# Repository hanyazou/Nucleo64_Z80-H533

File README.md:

# Nucleo64 Z80 H533

Nucleo64 Z80 H533 is a Z80 expansion board for the STM32 NUCLEO-H533RE that lets you run a real Z80 system with Microsoft BASIC and CP/M.

It combines a physical Z80 CPU, SRAM, and an STM32H533, which handles the I/O side at high speed.
With a microSD card, the board can boot CP/M directly, and it can even access a real USB floppy disk drive experimentally.

If you enjoy retro computers, homebrew hardware, or classic 8-bit systems, this board is a compact way to build and explore a modern Z80 machine.

Compared with the earlier <a href="https://github.com/hanyazou/Nucleo64_Z80">Nucleo64 Z80 project</a>,
this version provides faster I/O handling and adds a USB interface.

## Features

- Simple two-chip Z80 section using a Z80 CPU and SRAM
- Firmware includes Microsoft BASIC and an IPL (Initial Program Loader)
- Higher Z80 clock speed, up to 20 MHz
- microSD card over SPI for use as CP/M floppy disk images
- Experimental support for a real floppy disk drive over USB

This project is derived from satoshiokue's MEZ80RAM and SuperMEZ80-CPM.

## Appearance

The white boards shown in the following pictures are the Nucleo64 Z80 H533.

## Block Diagram

For more details, see the <a href="schematic.pdf">schematic (PDF)</a>.

## Required Components

### ICs

- U3 Z80, DIP-40, x1
- U2 AS6C4008-55 SRAM, 4 Mbit, DIP-32, x2

A Z80C0004 (4 MHz) or faster device is recommended.  
If you do not plan to run CP/M 3.0, even 512 Kbit (64 KB) SRAM may be sufficient.   

### Through-Hole Components

- U3 IC socket, DIP-40
- U2 IC socket, DIP-32
- C2, C3 0.1 uF ceramic capacitors
- C4 10 uF electrolytic capacitor
- R1 200 ohm, 1/6 W resistor
- R7, R8 100 ohm, 1/4 W resistors
- D3, D4 LEDs
- CN7, CN10 2x19 female pin sockets, 0.1 inch pitch

The resistor value for R7 and R8 may need to be adjusted depending on the LEDs you use.

### Surface-Mount Components

- U4 TPS22917DBV load switch, SOT-23-6 *3
- U5 74HCT153D, SOP-16 *4
- C1, C5 0.1 uF capacitors, 0603
- R2, R3 10 k ohm resistors, 0603

*3) This load switch turns the Z80-side power on and off from the STM32H533.  
It helps prevent 5 V from feeding back into the STM32 I/O pins and potentially damaging the MCU.  
The board may still work if 5 V and VCC are tied directly together, but that carries some risk to the STM32 and is not recommended.

*4) This logic IC is used for bank switching.  
If you do not need CP/M 3.0 support, you can omit U5 and short JP1 and JP2 instead.

### Optional Components

- J1, J2 1x20 pin headers, 0.1 inch pitch
- J3 JST SH 1.0 mm 4-pin connector
- J4 1x6 female pin socket, 0.1 inch pitch

J4 is for I2C Qwiic devices.  
For the microSD card slot, use the ARM/Arduino-compatible type shown on the following page:  
https://www.amazon.com/dp/B0B7WZQVHS

## Assembly Notes

With the small number of parts, assembly is straightforward.
Solder all components except the 2x19 pin headers first, then solder the pin headers last.

The 74HCT153 and TPS22917 parts I used had markings that made pin 1 orientation hard to identify.
The following photos show the orientation I used during assembly.

## NUCLEO Board Modification

ST occasionally revises Nucleo boards, and the hardware details can change slightly between revisions.
The board used here is marked:

`NUCLEO-H533RE NUH533RE$KR2 MB1814-H533RE-C02`

At the time of writing, there does not appear to be another NUCLEO-H533 variant.

On MB1814-H533RE-C02, GPIO pins PC14 and PC15 are connected to the OSC32 low-speed clock circuitry and are not routed to the Morpho connectors by default.
This project uses PC14 and PC15, so you need to rework the solder bridges:

- Remove SB30 and SB31
- Bridge SB29 and SB32

## Board Firmware

The `FW/projects/h533re` folder contains a STM32 firmware project for STM32CubeIDE.
The current target is the NUCLEO-H533RE.

The firmware includes Microsoft BASIC and an IPL.

### Change Z80 clock speed

The Z80 clock is generated by TIM2 in the STM32H533.
With a 248 MHz timer clock and a TIM2 counter period of 247, the output clock is 1 MHz, so the Z80 runs at 1 MHz.

If you change the counter period to 12, the Z80 clock becomes about 20 MHz.
In that case, the pulse value should be set to half of the counter period.
At 20 MHz, running `ASCIIARTM.BAS` takes about 60 seconds.

## Booting CP/M

You can run CP/M on the Z80 by connecting a microSD card slot to the SPI interface, writing a CP/M-80 disk image to the microSD card, and booting the board with that card inserted.

The disk images from <a href="https://github.com/hanyazou/SuperMEZ80">hanyazou/SuperMEZ80</a> can be used as-is.

## Connecting a Floppy Disk Drive

The STM32H533 has USB host capability.
In the photo above, a USB floppy disk drive is connected to the Nucleo board, and CP/M-80 is accessing the floppy disk.

Video: <a href="https://www.youtube.com/watch?v=yQrmxK0HUM0">YouTube</a>

In that video, CP/M boots from the microSD card as drive A:, and then displays the file list on the floppy disk drive assigned as drive C:.
You can also hear the drive access sounds.

The NUCLEO-H533RE board does not explicitly advertise USB host support, but it can operate as a USB host if 5 V is supplied to VBUS at the user USB connector.

The firmware has been tested experimentally with the following USB floppy disk drive, purchased from
<a href="https://amzn.asia/d/04LAehW9">Amazon.co.jp</a>:

- TEAC USB floppy disk drive
- Current support is read-only

```
Device VendorID/ProductID: 0x0644/0x0000 (TEAC Corporation)
Manufacturer String:      1 "TEACV0.0"
Product String:           2 "TEACV0.0"
```

To supply 5 V to VBUS from the USB Type-C connector, short both settings in the NUCLEO power source selection header `JP5`:

- `5V_STLK` to power the STM32 side from the ST-LINK 5 V supply
- `VBUSC` to route power to the user USB connector `CN3`

With both jumpers set, the ST-LINK 5 V supply is fed to `CN3` VBUS.

Be careful here: if you connect `CN3` to a PC or any other device that also drives 5 V onto VBUS in this configuration, you could damage the Nucleo board, the connected device, or both.
Do not connect `CN3` to a host PC while this power configuration is in place.

## References

### SuperMEZ80-CPM

https://github.com/hanyazou/SuperMEZ80-CPM

### EMUZ80

https://vintagechips.wordpress.com/2022/03/05/emuz80_reference/

### MEZ80RAM

https://github.com/satoshiokue/MEZ80RAM

### Nucleo STM32H533RE

#### Board

https://www.st.com/en/evaluation-tools/nucleo-h533re.html

#### Schematic

<a href="https://www.st.com/content/ccc/resource/technical/layouts_and_diagrams/schematic_pack/group2/58/61/64/9a/03/20/4f/84/mb1814-h533re-c02-schematic/files/mb1814-h533re-c02-schematic.pdf/jcr:content/translations/en.mb1814-h533re-c02-schematic.pdf">MB1814</a>

#### User Manual

<a href="https://www.st.com/content/ccc/resource/technical/document/user_manual/group2/86/81/52/e6/5d/f1/46/9e/DM00941891/files/DM00941891.pdf/jcr:content/translations/en.DM00941891.pdf">UM3121</a>

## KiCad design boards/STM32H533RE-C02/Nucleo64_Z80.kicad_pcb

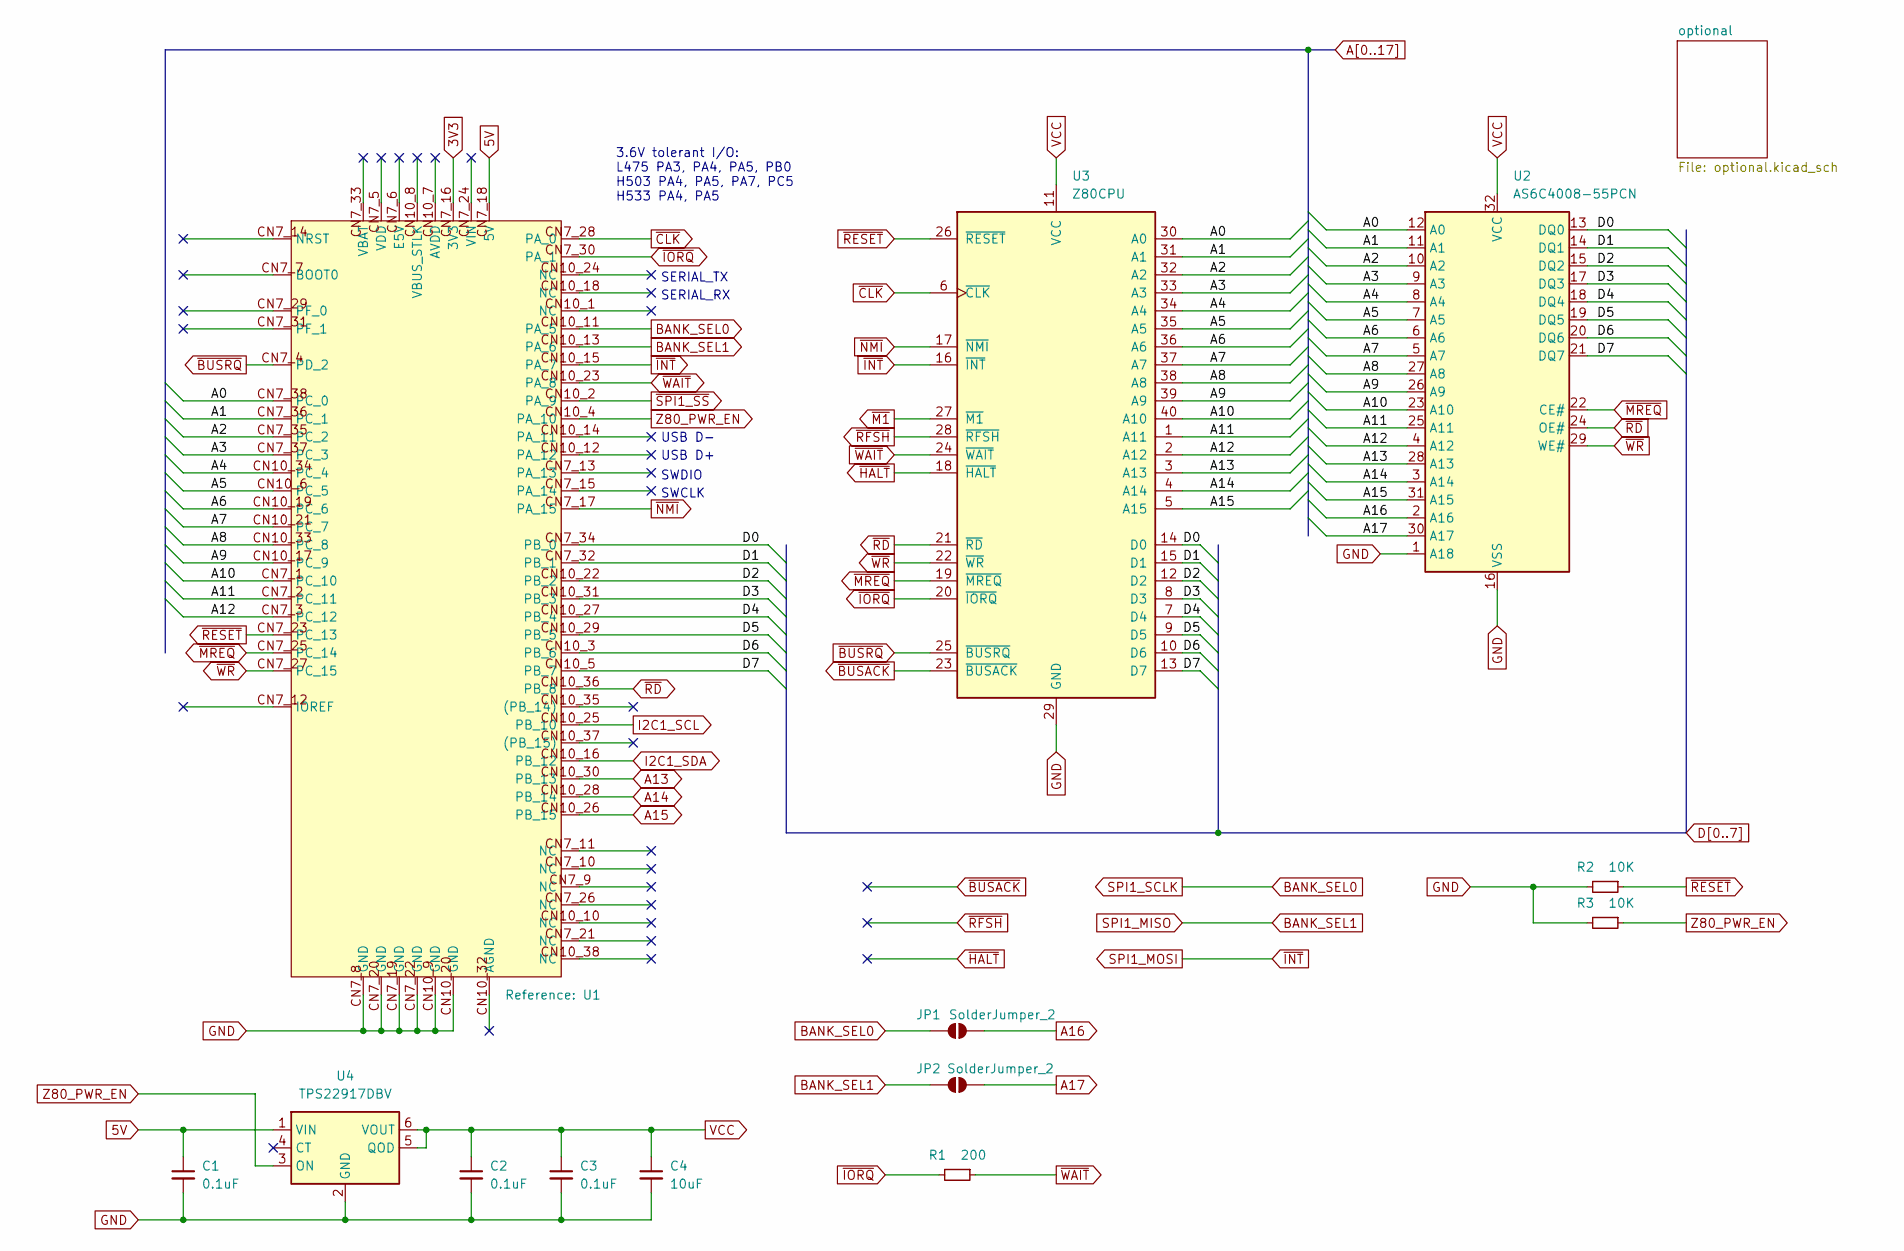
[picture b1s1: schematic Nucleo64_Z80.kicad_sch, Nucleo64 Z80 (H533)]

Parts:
C1: 0.1uF; C_0603_1608Metric_Pad1.08x0.95mm_HandSolder
C2, C3: 0.1uF; C_Disc_D3.8mm_W2.6mm_P2.50mm
C4: 10uF; CP_Radial_D5.0mm_P2.50mm
JP1, JP2: SolderJumper_2; SolderJumper-2_P1.3mm_Open_TrianglePad1.0x1.5mm
R1: 200; R_Axial_DIN0204_L3.6mm_D1.6mm_P7.62mm_Horizontal
R2, R3: 10K; R_0603_1608Metric_Pad0.98x0.95mm_HandSolder
U1: NUCLEO64_morpho
U2: AS6C4008-55PCN; DIP-32_W15.24mm
U3: Z80CPU; DIP-40_W15.24mm
U4: TPS22917DBV; SOT-23-6

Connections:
3V3: U1.CN7_16 (3V3); also elsewhere on the board
5V: C1.1, U1.CN7_18 (5V), U4.1 (VIN)
A0: U1.CN7_38 (PC_0), U2.12 (A0), U3.30 (A0); also elsewhere on the board
A1: U1.CN7_36 (PC_1), U2.11 (A1), U3.31 (A1); also elsewhere on the board
A2: U1.CN7_35 (PC_2), U2.10 (A2), U3.32 (A2); also elsewhere on the board
A3: U1.CN7_37 (PC_3), U2.9 (A3), U3.33 (A3); also elsewhere on the board
A4: U1.CN10_34 (PC_4), U2.8 (A4), U3.34 (A4); also elsewhere on the board
A5: U1.CN10_6 (PC_5), U2.7 (A5), U3.35 (A5); also elsewhere on the board
A6: U1.CN10_19 (PC_6), U2.6 (A6), U3.36 (A6); also elsewhere on the board
A7: U1.CN10_21 (PC_7), U2.5 (A7), U3.37 (A7); also elsewhere on the board
A8: U1.CN10_33 (PC_8), U2.27 (A8), U3.38 (A8); also elsewhere on the board
A9: U1.CN10_17 (PC_9), U2.26 (A9), U3.39 (A9); also elsewhere on the board
A10: U1.CN7_1 (PC_10), U2.23 (A10), U3.40 (A10); also elsewhere on the board
A11: U1.CN7_2 (PC_11), U2.25 (A11), U3.1 (A11); also elsewhere on the board
A12: U1.CN7_3 (PC_12), U2.4 (A12), U3.2 (A12); also elsewhere on the board
A13: U1.CN10_30 (PB_13), U2.28 (A13), U3.3 (A13); also elsewhere on the board
A14: U1.CN10_28 (PB_14), U2.3 (A14), U3.4 (A14); also elsewhere on the board
A15: U1.CN10_26 (PB_15), U2.31 (A15), U3.5 (A15); also elsewhere on the board
A16: JP1.2 (B), U2.2 (A16); also elsewhere on the board
A17: JP2.2 (B), U2.30 (A17); also elsewhere on the board
BANK_SEL0: JP1.1 (A), U1.CN10_11 (PA_5); also elsewhere on the board
BANK_SEL1: JP2.1 (A), U1.CN10_13 (PA_6); also elsewhere on the board
D0: U1.CN7_34 (PB_0), U2.13 (DQ0), U3.14 (D0); also elsewhere on the board
D1: U1.CN7_32 (PB_1), U2.14 (DQ1), U3.15 (D1); also elsewhere on the board
D2: U1.CN10_22 (PB_2), U2.15 (DQ2), U3.12 (D2); also elsewhere on the board
D3: U1.CN10_31 (PB_3), U2.17 (DQ3), U3.8 (D3); also elsewhere on the board
D4: U1.CN10_27 (PB_4), U2.18 (DQ4), U3.7 (D4); also elsewhere on the board
D5: U1.CN10_29 (PB_5), U2.19 (DQ5), U3.9 (D5); also elsewhere on the board
D6: U1.CN10_3 (PB_6), U2.20 (DQ6), U3.10 (D6); also elsewhere on the board
D7: U1.CN10_5 (PB_7), U2.21 (DQ7), U3.13 (D7); also elsewhere on the board
GND: C1.2, C2.2, C3.2, C4.2, R2.2, R3.2, U1.CN7_8 (GND), U1.CN7_19 (GND), U1.CN7_20 (GND), U1.CN7_22 (GND), U1.CN10_9 (GND), U1.CN10_20 (GND), U2.1 (A18), U2.16 (VSS), U3.29 (GND), U4.2 (GND); also elsewhere on the board
I2C1_SCL: U1.CN10_25 (PB_10); also elsewhere on the board
I2C1_SDA: U1.CN10_16 (PB_12); also elsewhere on the board
SPI1_MOSI: U1.CN10_15 (PA_7), U3.16 (~INT); also elsewhere on the board
VCC: C2.1, C3.1, C4.1, U2.32 (VCC), U3.11 (VCC), U4.5 (QOD), U4.6 (VOUT); also elsewhere on the board
Z80_PWR_EN: R3.1, U1.CN10_4 (PA_10), U4.3 (ON)
~BUSACK: U3.23 (~BUSACK); also elsewhere on the board
~BUSRQ: U1.CN7_4 (PD_2), U3.25 (~BUSRQ); also elsewhere on the board
~CLK: U1.CN7_28 (PA_0), U3.6 (~CLK); also elsewhere on the board
~HALT: U3.18 (~HALT); also elsewhere on the board
~IORQ: R1.2, U1.CN7_30 (PA_1), U3.20 (~IORQ); also elsewhere on the board
~M1: U3.27 (~M1); also elsewhere on the board
~MREQ: U1.CN7_25 (PC_14), U2.22 (CE#), U3.19 (~MREQ); also elsewhere on the board
~NMI: U1.CN7_17 (PA_15), U3.17 (~NMI); also elsewhere on the board
~RD: U1.CN10_36 (PB_8), U2.24 (OE#), U3.21 (~RD); also elsewhere on the board
~RESET: R2.1, U1.CN7_23 (PC_13), U3.26 (~RESET); also elsewhere on the board
~RFSH: U3.28 (~RFSH); also elsewhere on the board
~SPI1_SS: U1.CN10_2 (PA_9); also elsewhere on the board
~WAIT: R1.1, U1.CN10_23 (PA_8), U3.24 (~WAIT); also elsewhere on the board
~WR: U1.CN7_27 (PC_15), U2.29 (WE#), U3.22 (~WR); also elsewhere on the board

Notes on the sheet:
SWDIO
SERIAL_RX
USB D+
USB D-
SERIAL_TX
SWCLK
3.6V tolerant I/O: L475 PA3, PA4, PA5, PB0 H503 PA4, PA5, PA7, PC5 H533 PA4, PA5

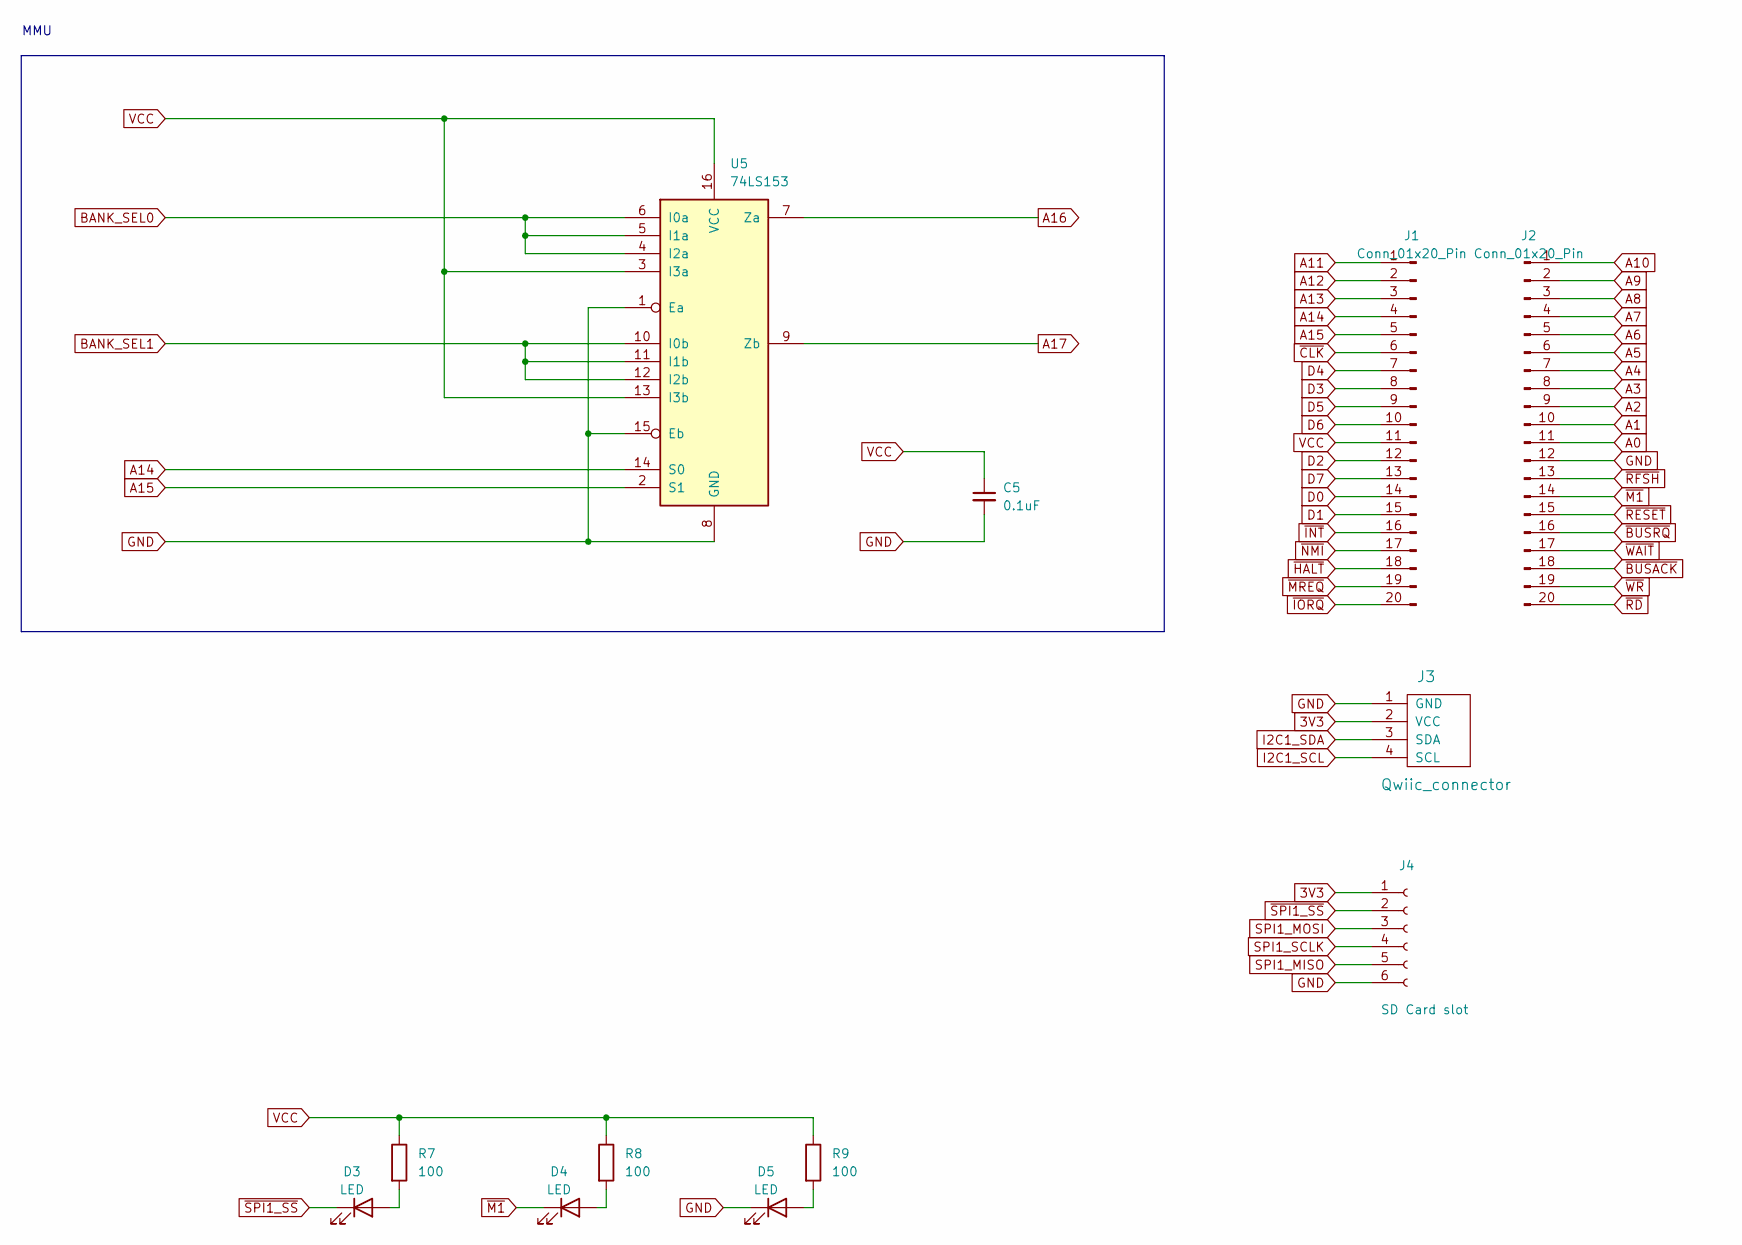
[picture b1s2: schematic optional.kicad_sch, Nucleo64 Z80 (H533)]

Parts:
C5: 0.1uF; C_0603_1608Metric_Pad1.08x0.95mm_HandSolder
D3, D4, D5: LED; LED_D5.0mm
J1, J2: Conn_01x20_Pin; PinHeader_1x20_P2.54mm_Vertical
J3: Qwiic_connector; Qwiic_I2C_1.00mm_4pin
J4: SD Card slot; PinHeader_1x06_P2.54mm_Vertical
R7, R8, R9: 100; R_Axial_DIN0204_L3.6mm_D1.6mm_P7.62mm_Horizontal
U5: 74LS153; SOP-16_4.55x10.3mm_P1.27mm

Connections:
3V3: J3.2 (VCC), J4.1; also elsewhere on the board
A0: J2.11; also elsewhere on the board
A1: J2.10; also elsewhere on the board
A2: J2.9; also elsewhere on the board
A3: J2.8; also elsewhere on the board
A4: J2.7; also elsewhere on the board
A5: J2.6; also elsewhere on the board
A6: J2.5; also elsewhere on the board
A7: J2.4; also elsewhere on the board
A8: J2.3; also elsewhere on the board
A9: J2.2; also elsewhere on the board
A10: J2.1; also elsewhere on the board
A11: J1.1; also elsewhere on the board
A12: J1.2; also elsewhere on the board
A13: J1.3; also elsewhere on the board
A14: J1.4, U5.14 (S0); also elsewhere on the board
A15: J1.5, U5.2 (S1); also elsewhere on the board
A16: U5.7 (Za); also elsewhere on the board
A17: U5.9 (Zb); also elsewhere on the board
BANK_SEL0: J4.4, U5.4 (I2a), U5.5 (I1a), U5.6 (I0a); also elsewhere on the board
BANK_SEL1: J4.5, U5.10 (I0b), U5.11 (I1b), U5.12 (I2b); also elsewhere on the board
D0: J1.14; also elsewhere on the board
D1: J1.15; also elsewhere on the board
D2: J1.12; also elsewhere on the board
D3: J1.8; also elsewhere on the board
D4: J1.7; also elsewhere on the board
D5: J1.9; also elsewhere on the board
D6: J1.10; also elsewhere on the board
D7: J1.13; also elsewhere on the board
GND: C5.2, D5.1 (K), J2.12, J3.1 (GND), J3.6, J4.6, U5.1 (Ea), U5.8 (GND), U5.15 (Eb); also elsewhere on the board
I2C1_SCL: J3.4 (SCL); also elsewhere on the board
I2C1_SDA: J3.3 (SDA); also elsewhere on the board
unnamed: D3.2 (A), R7.2
unnamed: D4.2 (A), R8.2
unnamed: D5.2 (A), R9.2
SPI1_MOSI: J1.16, J4.3; also elsewhere on the board
VCC: C5.1, J1.11, R7.1, R8.1, R9.1, U5.3 (I3a), U5.13 (I3b), U5.16 (VCC); also elsewhere on the board
~BUSACK: J2.18; also elsewhere on the board
~BUSRQ: J2.16; also elsewhere on the board
~CLK: J1.6; also elsewhere on the board
~HALT: J1.18; also elsewhere on the board
~IORQ: J1.20; also elsewhere on the board
~M1: D4.1 (K), J2.14; also elsewhere on the board
~MREQ: J1.19; also elsewhere on the board
~NMI: J1.17; also elsewhere on the board
~RD: J2.20; also elsewhere on the board
~RESET: J2.15; also elsewhere on the board
~RFSH: J2.13; also elsewhere on the board
~SPI1_SS: D3.1 (K), J4.2; also elsewhere on the board
~WAIT: J2.17; also elsewhere on the board
~WR: J2.19; also elsewhere on the board

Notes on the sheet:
MMU

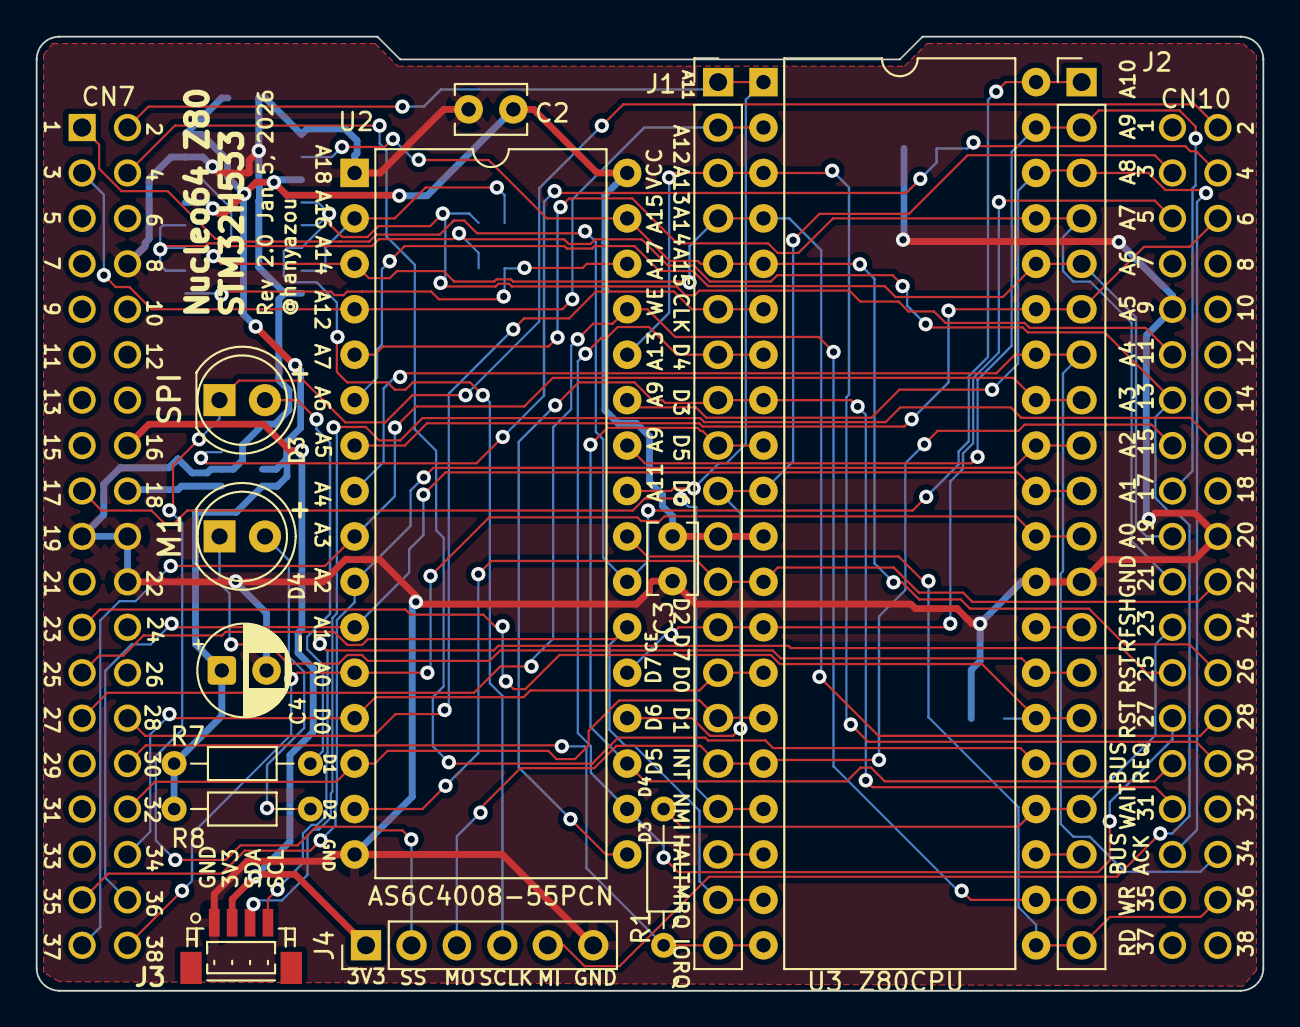
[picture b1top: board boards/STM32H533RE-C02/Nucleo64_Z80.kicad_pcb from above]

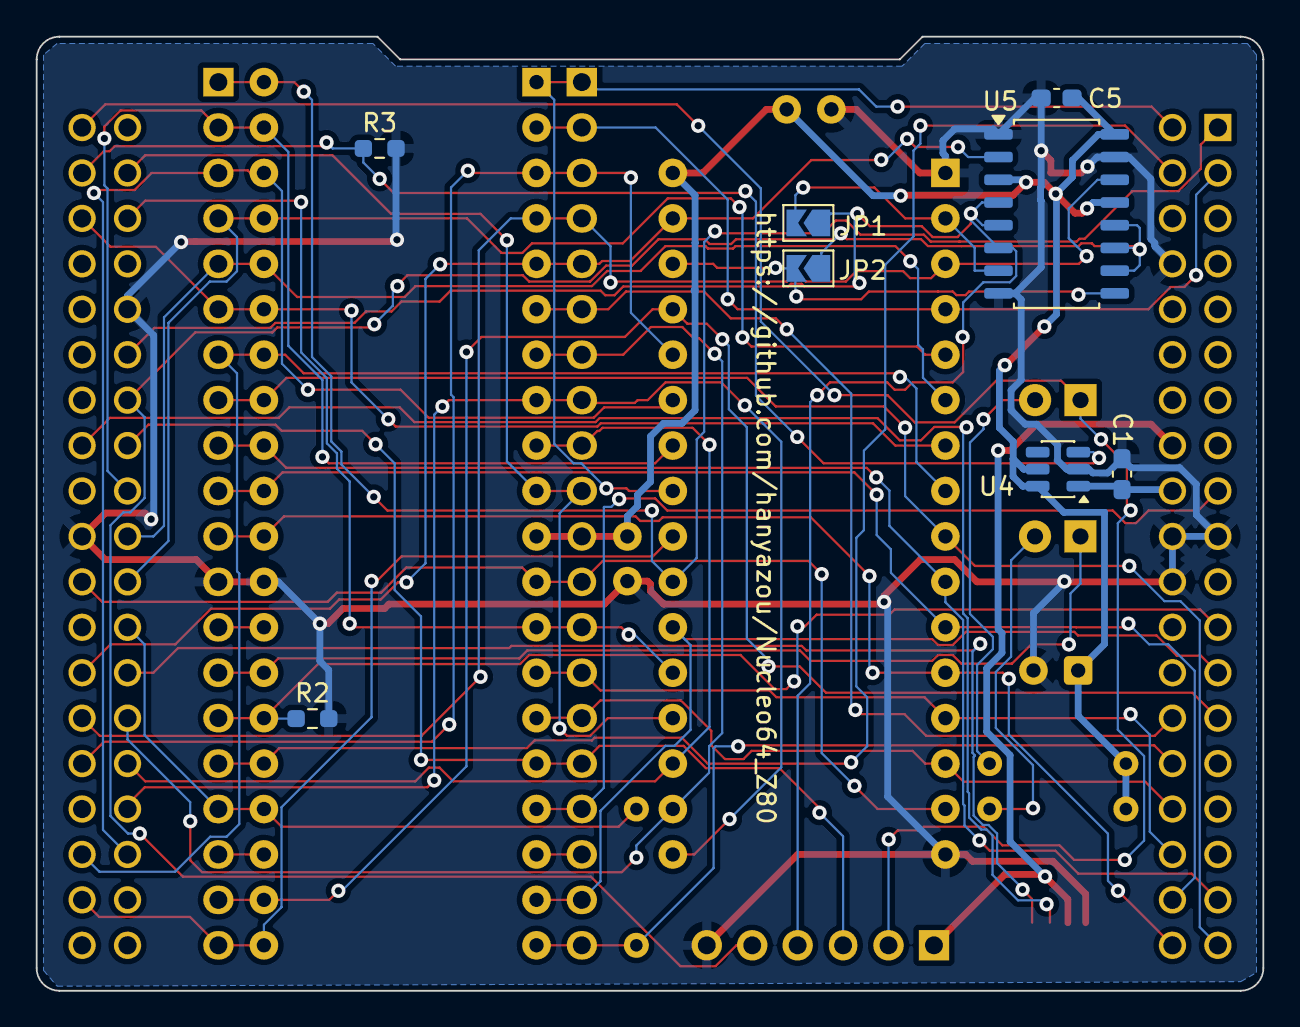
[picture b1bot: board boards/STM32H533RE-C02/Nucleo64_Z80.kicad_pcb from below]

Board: 2 copper layers, 68.6 x 53.3 mm, 23 parts (8 on the bottom side), 52 nets.

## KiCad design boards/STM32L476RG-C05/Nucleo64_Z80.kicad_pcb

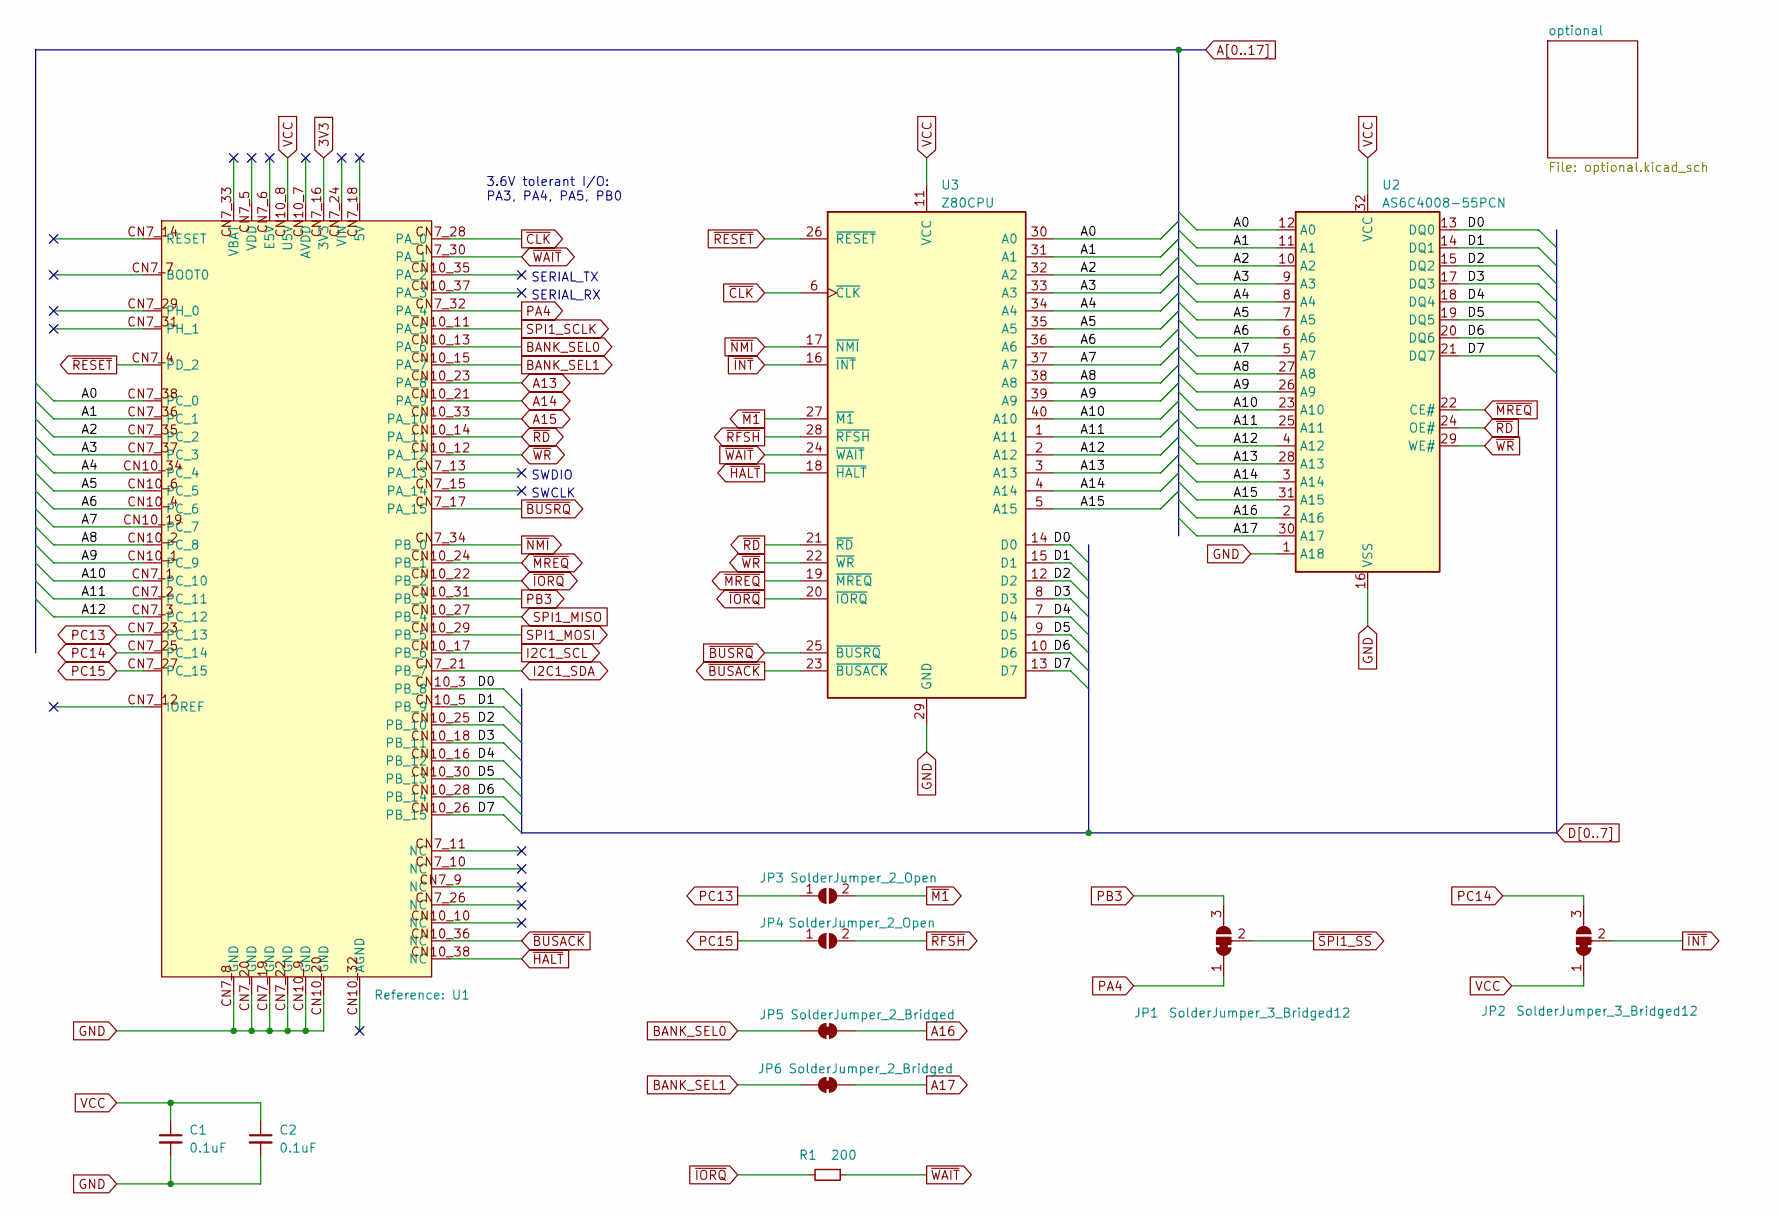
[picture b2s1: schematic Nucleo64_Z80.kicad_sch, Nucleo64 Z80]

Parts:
C1, C2: 0.1uF; C_Disc_D3.8mm_W2.6mm_P2.50mm
JP1, JP2: SolderJumper_3_Bridged12; SolderJumper-3_P1.3mm_Bridged12_RoundedPad1.0x1.5mm_NumberL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
JP3, JP4: SolderJumper_2_Open; SolderJumper-2_P1.3mm_Open_RoundedPad1.0x1.5mm
JP5, JP6: SolderJumper_2_Bridged; SolderJumper-2_P1.3mm_Bridged_RoundedPad1.0x1.5mm
R1: 200; R_Axial_DIN0204_L3.6mm_D1.6mm_P7.62mm_Horizontal
U1: NUCLEO64_morpho
U2: AS6C4008-55PCN; DIP-32_W15.24mm
U3: Z80CPU; DIP-40_W15.24mm

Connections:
3V3: U1.CN7_16 (3V3); also elsewhere on the board
A0: U1.CN7_38 (PC_0), U2.12 (A0), U3.30 (A0); also elsewhere on the board
A1: U1.CN7_36 (PC_1), U2.11 (A1), U3.31 (A1); also elsewhere on the board
A2: U1.CN7_35 (PC_2), U2.10 (A2), U3.32 (A2); also elsewhere on the board
A3: U1.CN7_37 (PC_3), U2.9 (A3), U3.33 (A3); also elsewhere on the board
A4: U1.CN10_34 (PC_4), U2.8 (A4), U3.34 (A4); also elsewhere on the board
A5: U1.CN10_6 (PC_5), U2.7 (A5), U3.35 (A5); also elsewhere on the board
A6: U1.CN10_4 (PC_6), U2.6 (A6), U3.36 (A6); also elsewhere on the board
A7: U1.CN10_19 (PC_7), U2.5 (A7), U3.37 (A7); also elsewhere on the board
A8: U1.CN10_2 (PC_8), U2.27 (A8), U3.38 (A8); also elsewhere on the board
A9: U1.CN10_1 (PC_9), U2.26 (A9), U3.39 (A9); also elsewhere on the board
A10: U1.CN7_1 (PC_10), U2.23 (A10), U3.40 (A10); also elsewhere on the board
A11: U1.CN7_2 (PC_11), U2.25 (A11), U3.1 (A11); also elsewhere on the board
A12: U1.CN7_3 (PC_12), U2.4 (A12), U3.2 (A12); also elsewhere on the board
A13: U1.CN10_23 (PA_8), U2.28 (A13), U3.3 (A13); also elsewhere on the board
A14: U1.CN10_21 (PA_9), U2.3 (A14), U3.4 (A14); also elsewhere on the board
A15: U1.CN10_33 (PA_10), U2.31 (A15), U3.5 (A15); also elsewhere on the board
A16: JP5.2 (B), U2.2 (A16); also elsewhere on the board
A17: JP6.2 (B), U2.30 (A17); also elsewhere on the board
BANK_SEL0: JP5.1 (A), U1.CN10_13 (PA_6); also elsewhere on the board
BANK_SEL1: JP6.1 (A), U1.CN10_15 (PA_7); also elsewhere on the board
D0: U1.CN10_3 (PB_8), U2.13 (DQ0), U3.14 (D0); also elsewhere on the board
D1: U1.CN10_5 (PB_9), U2.14 (DQ1), U3.15 (D1); also elsewhere on the board
D2: U1.CN10_25 (PB_10), U2.15 (DQ2), U3.12 (D2); also elsewhere on the board
D3: U1.CN10_18 (PB_11), U2.17 (DQ3), U3.8 (D3); also elsewhere on the board
D4: U1.CN10_16 (PB_12), U2.18 (DQ4), U3.7 (D4); also elsewhere on the board
D5: U1.CN10_30 (PB_13), U2.19 (DQ5), U3.9 (D5); also elsewhere on the board
D6: U1.CN10_28 (PB_14), U2.20 (DQ6), U3.10 (D6); also elsewhere on the board
D7: U1.CN10_26 (PB_15), U2.21 (DQ7), U3.13 (D7); also elsewhere on the board
GND: C1.2, C2.2, U1.CN7_8 (GND), U1.CN7_19 (GND), U1.CN7_20 (GND), U1.CN7_22 (GND), U1.CN10_9 (GND), U1.CN10_20 (GND), U2.1 (A18), U2.16 (VSS), U3.29 (GND); also elsewhere on the board
I2C1_SCL: U1.CN10_17 (PB_6); also elsewhere on the board
I2C1_SDA: U1.CN7_21 (PB_7); also elsewhere on the board
PA4: JP1.1 (A), U1.CN7_32 (PA_4)
PB3: JP1.3 (B), U1.CN10_31 (PB_3)
PC13: JP3.1 (A), U1.CN7_23 (PC_13)
PC14: JP2.3 (B), U1.CN7_25 (PC_14)
PC15: JP4.1 (A), U1.CN7_27 (PC_15)
SPI1_MISO: U1.CN10_27 (PB_4); also elsewhere on the board
SPI1_MOSI: U1.CN10_29 (PB_5); also elsewhere on the board
SPI1_SCLK: U1.CN10_11 (PA_5); also elsewhere on the board
VCC: C1.1, C2.1, JP2.1 (A), U1.CN10_8 (U5V), U2.32 (VCC), U3.11 (VCC); also elsewhere on the board
~BUSACK: U1.CN10_36 (NC), U3.23 (~BUSACK); also elsewhere on the board
~BUSRQ: U1.CN7_17 (PA_15), U3.25 (~BUSRQ); also elsewhere on the board
~CLK: U1.CN7_28 (PA_0), U3.6 (~CLK); also elsewhere on the board
~HALT: U1.CN10_38 (NC), U3.18 (~HALT); also elsewhere on the board
~INT: JP2.2 (C), U3.16 (~INT); also elsewhere on the board
~IORQ: R1.2, U1.CN10_22 (PB_2), U3.20 (~IORQ); also elsewhere on the board
~M1: JP3.2 (B), U3.27 (~M1); also elsewhere on the board
~MREQ: U1.CN10_24 (PB_1), U2.22 (CE#), U3.19 (~MREQ); also elsewhere on the board
~NMI: U1.CN7_34 (PB_0), U3.17 (~NMI); also elsewhere on the board
~RD: U1.CN10_14 (PA_11), U2.24 (OE#), U3.21 (~RD); also elsewhere on the board
~RESET: U1.CN7_4 (PD_2), U3.26 (~RESET); also elsewhere on the board
~RFSH: JP4.2 (B), U3.28 (~RFSH); also elsewhere on the board
~SPI1_SS: JP1.2 (C); also elsewhere on the board
~WAIT: R1.1, U1.CN7_30 (PA_1), U3.24 (~WAIT); also elsewhere on the board
~WR: U1.CN10_12 (PA_12), U2.29 (WE#), U3.22 (~WR); also elsewhere on the board

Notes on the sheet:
SWDIO
SERIAL_RX
SERIAL_TX
SWCLK
3.6V tolerant I/O: PA3, PA4, PA5, PB0

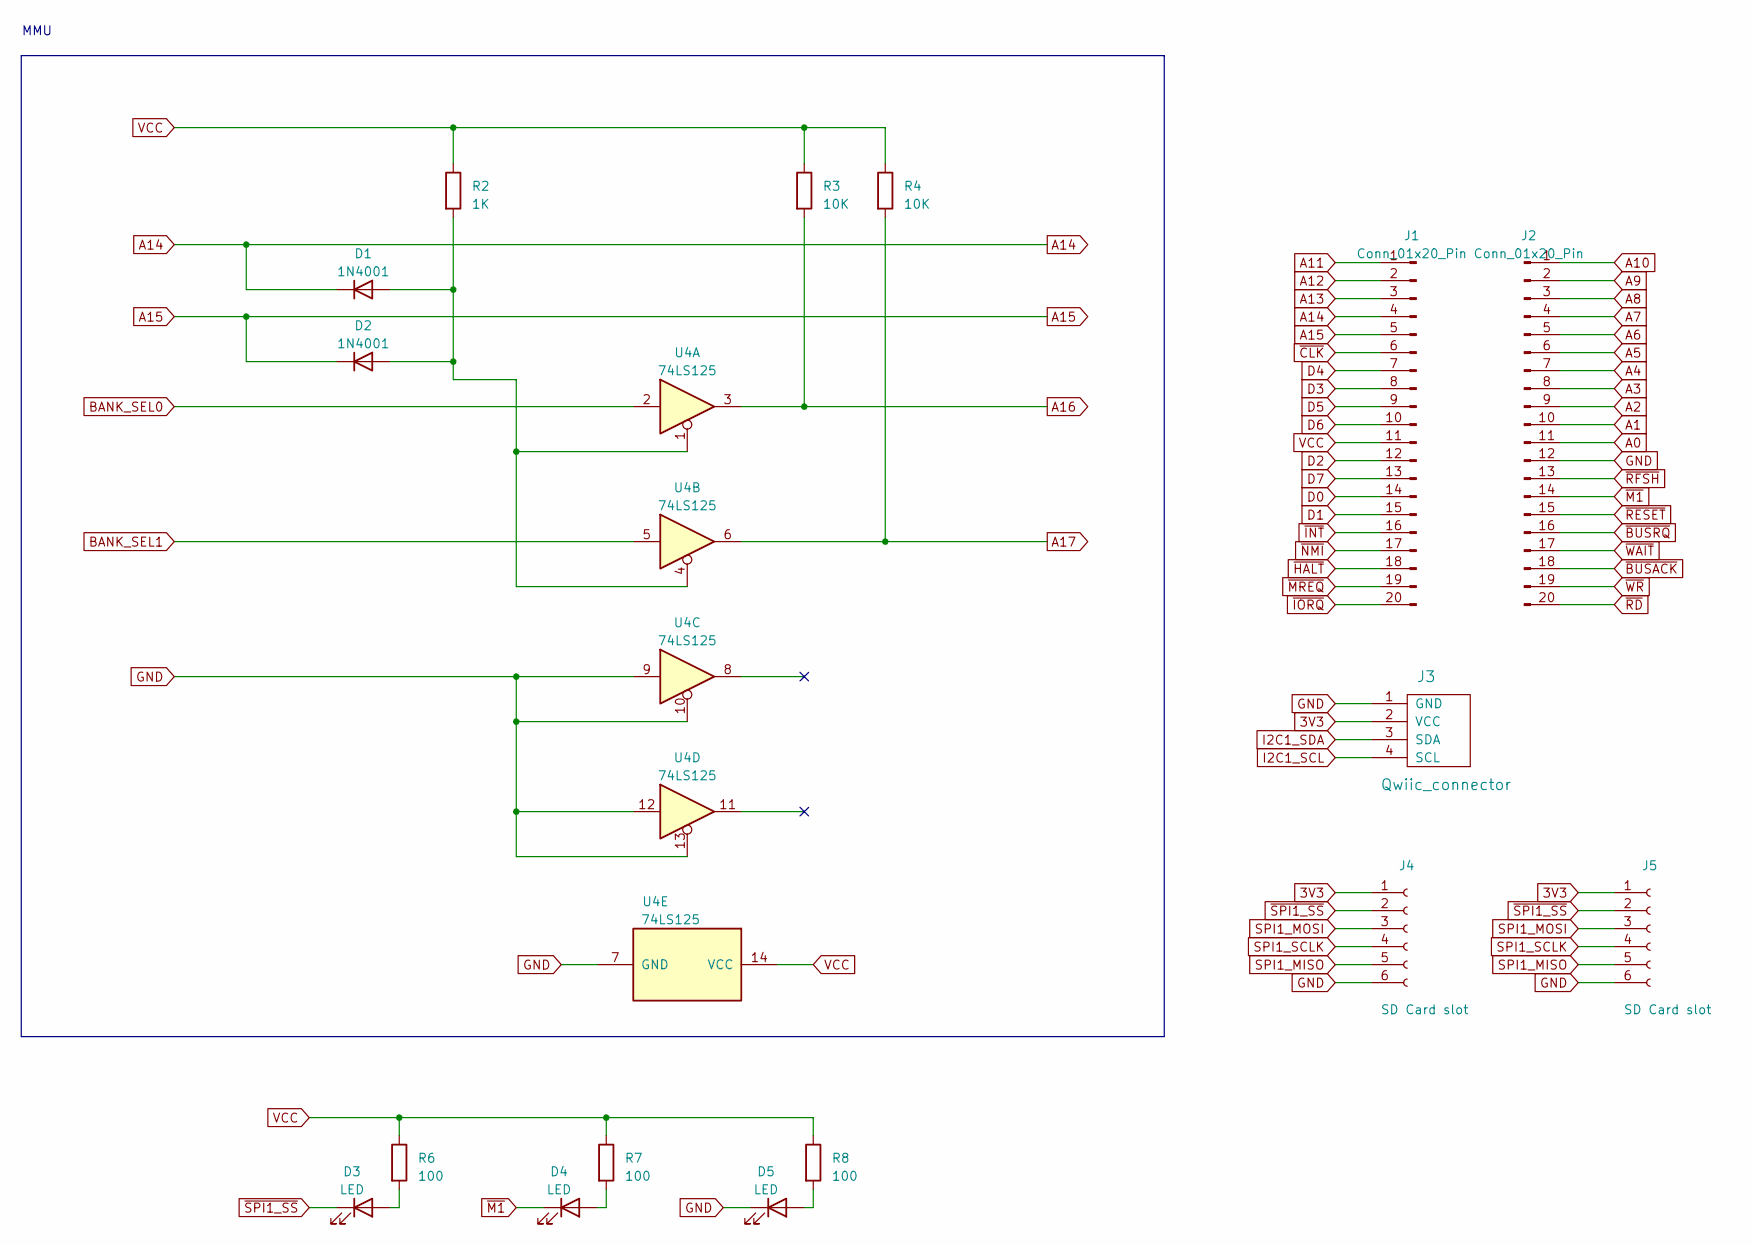
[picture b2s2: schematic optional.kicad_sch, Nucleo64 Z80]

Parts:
D1, D2: 1N4001; D_0805_2012Metric_Pad1.15x1.40mm_HandSolder
D3, D4, D5: LED; LED_D5.0mm
J1, J2: Conn_01x20_Pin; PinHeader_1x20_P2.54mm_Vertical
J3: Qwiic_connector; Qwiic_I2C_1.00mm_4pin
J4, J5: SD Card slot; PinHeader_1x06_P2.54mm_Vertical
R2: 1K; R_0805_2012Metric_Pad1.20x1.40mm_HandSolder
R3, R4: 10K; R_0805_2012Metric_Pad1.20x1.40mm_HandSolder
R6, R7, R8: 100; R_Axial_DIN0204_L3.6mm_D1.6mm_P7.62mm_Horizontal
U4: 74LS125; SSOP-14_5.3x6.2mm_P0.65mm

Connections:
3V3: J3.2 (VCC), J4.1, J5.1; also elsewhere on the board
A0: J2.11; also elsewhere on the board
A1: J2.10; also elsewhere on the board
A2: J2.9; also elsewhere on the board
A3: J2.8; also elsewhere on the board
A4: J2.7; also elsewhere on the board
A5: J2.6; also elsewhere on the board
A6: J2.5; also elsewhere on the board
A7: J2.4; also elsewhere on the board
A8: J2.3; also elsewhere on the board
A9: J2.2; also elsewhere on the board
A10: J2.1; also elsewhere on the board
A11: J1.1; also elsewhere on the board
A12: J1.2; also elsewhere on the board
A13: J1.3; also elsewhere on the board
A14: D1.1 (K), J1.4; also elsewhere on the board
A15: D2.1 (K), J1.5; also elsewhere on the board
A16: R3.2, U4.3; also elsewhere on the board
A17: R4.2, U4.6; also elsewhere on the board
BANK_SEL0: U4.2; also elsewhere on the board
BANK_SEL1: U4.5; also elsewhere on the board
D0: J1.14; also elsewhere on the board
D1: J1.15; also elsewhere on the board
D2: J1.12; also elsewhere on the board
D3: J1.8; also elsewhere on the board
D4: J1.7; also elsewhere on the board
D5: J1.9; also elsewhere on the board
D6: J1.10; also elsewhere on the board
D7: J1.13; also elsewhere on the board
GND: D5.1 (K), J2.12, J3.1 (GND), J4.6, J5.6, U4.7 (GND), U4.9, U4.10, U4.12, U4.13; also elsewhere on the board
I2C1_SCL: J3.4 (SCL); also elsewhere on the board
I2C1_SDA: J3.3 (SDA); also elsewhere on the board
unnamed: D1.2 (A), D2.2 (A), R2.2, U4.1, U4.4
unnamed: D3.2 (A), R6.2
unnamed: D4.2 (A), R7.2
unnamed: D5.2 (A), R8.2
SPI1_MISO: J4.5, J5.5; also elsewhere on the board
SPI1_MOSI: J4.3, J5.3; also elsewhere on the board
SPI1_SCLK: J4.4, J5.4; also elsewhere on the board
VCC: J1.11, R2.1, R3.1, R4.1, R6.1, R7.1, R8.1, U4.14 (VCC); also elsewhere on the board
~BUSACK: J2.18; also elsewhere on the board
~BUSRQ: J2.16; also elsewhere on the board
~CLK: J1.6; also elsewhere on the board
~HALT: J1.18; also elsewhere on the board
~INT: J1.16; also elsewhere on the board
~IORQ: J1.20; also elsewhere on the board
~M1: D4.1 (K), J2.14; also elsewhere on the board
~MREQ: J1.19; also elsewhere on the board
~NMI: J1.17; also elsewhere on the board
~RD: J2.20; also elsewhere on the board
~RESET: J2.15; also elsewhere on the board
~RFSH: J2.13; also elsewhere on the board
~SPI1_SS: D3.1 (K), J4.2, J5.2; also elsewhere on the board
~WAIT: J2.17; also elsewhere on the board
~WR: J2.19; also elsewhere on the board

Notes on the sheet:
MMU
